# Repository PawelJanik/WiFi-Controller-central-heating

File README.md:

WiFi controller (central heating)

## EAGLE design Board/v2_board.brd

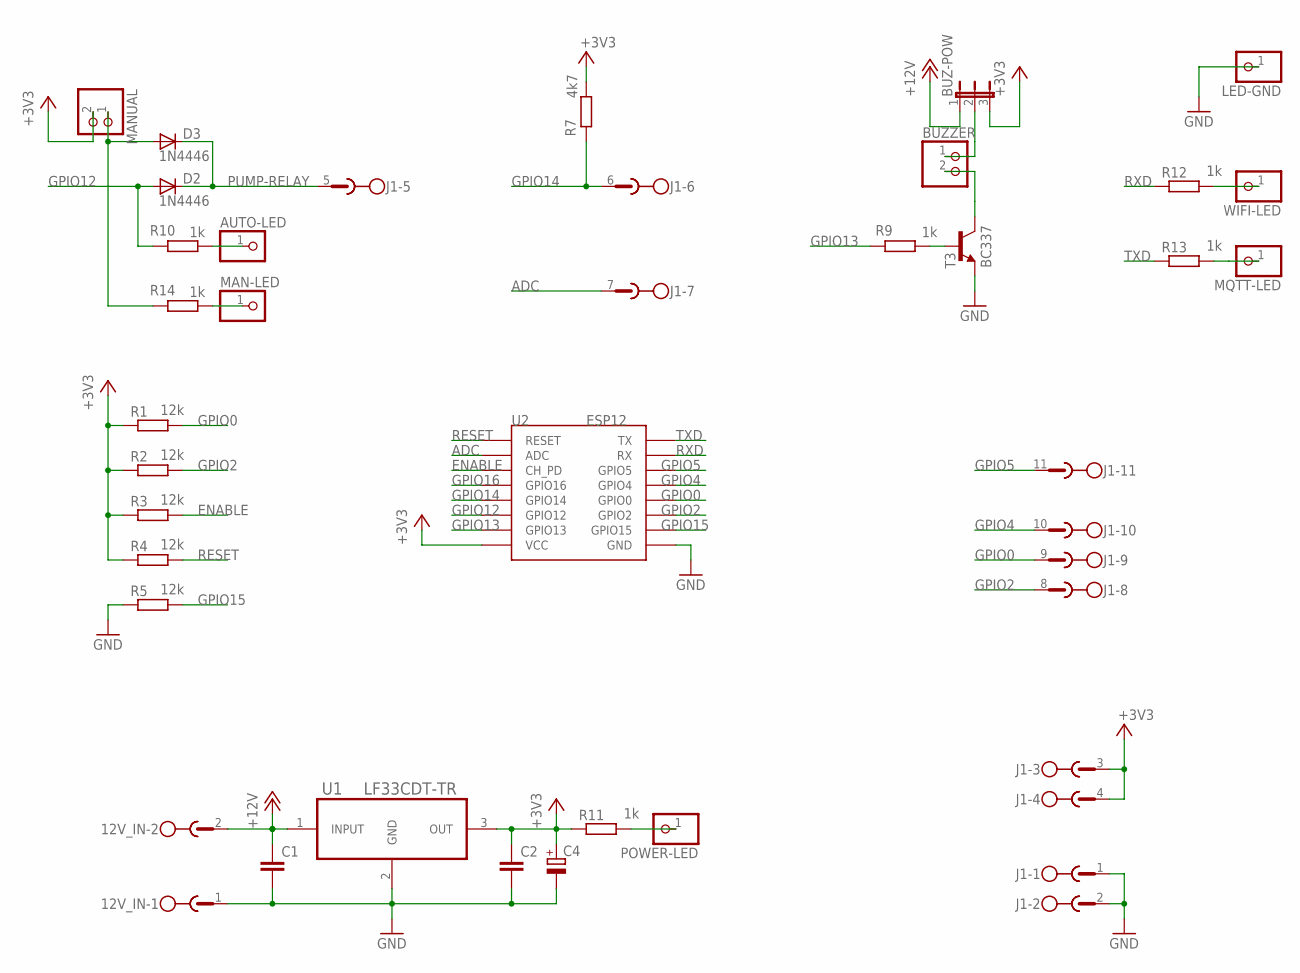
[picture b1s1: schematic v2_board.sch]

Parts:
12V_IN: MSTBA2
AUTO-LED: PINHD-1X1; 1X01
BUZ-POW: JP2E; JP2
BUZZER: PINHD-1X2; 1X02
C1, C2: C-EU025-025X050; C025-025X050
C4: CPOL-EUE3.5-8; E3,5-8
D2, D3: 1N4446; DO35-10
J1: MSTBA11
LED-GND: PINHD-1X1; 1X01
MAN-LED: PINHD-1X1; 1X01
MANUAL: PINHD-1X2; 1X02
MQTT-LED: PINHD-1X1; 1X01
POWER-LED: PINHD-1X1; 1X01
R1, R2, R3, R4, R5: 12k; R1206
R7: 4k7; R1206
R9, R10, R11, R12, R13, R14: 1k; R1206
T3: BC337; TO92
U1: LF33CDT-TR; TO228P972X240-3N
U2: ESP12
WIFI-LED: PINHD-1X1; 1X01

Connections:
+3V3: BUZ-POW.3, C2.1, C4.+, J1.3, J1.4, MANUAL.2, R1.1, R2.1, R3.1, R4.1, R7.1, R11.1, U1.3 (OUT), U2.VCC
+12V: 12V_IN.2, BUZ-POW.1, C1.1, U1.1 (INPUT)
ADC: J1.7, U2.ADC
ENABLE: R3.2, U2.CH_PD
GND: 12V_IN.1, C1.2, C2.2, C4.-, J1.1, J1.2, LED-GND.1, R5.1, T3.1 (E), U1.2 (GND), U2.GND
GPIO0: J1.9, R1.2, U2.GPIO0
GPIO2: J1.8, R2.2, U2.GPIO2
GPIO4: J1.10, U2.GPIO5 (GPIO4)
GPIO5: J1.11, U2.GPIO4 (GPIO5)
GPIO12: D2.A, R10.2, U2.GPIO12
GPIO13: R9.2, U2.GPIO13
GPIO14: J1.6, R7.2, U2.GPIO14
GPIO15: R5.2, U2.GPIO15
GPIO16: U2.GPIO16
unnamed: D3.A, MANUAL.1, R14.2
unnamed: BUZZER.2, T3.3 (C)
unnamed: R9.1, T3.2 (B)
unnamed: BUZ-POW.2, BUZZER.1
unnamed: POWER-LED.1, R11.2
unnamed: R12.2, WIFI-LED.1
unnamed: MQTT-LED.1, R13.2
unnamed: AUTO-LED.1, R10.1
unnamed: MAN-LED.1, R14.1
PUMP-RELAY: D2.C, D3.C, J1.5
RESET: R4.2, U2.RESET
RXD: R12.1, U2.RX
TXD: R13.1, U2.TX

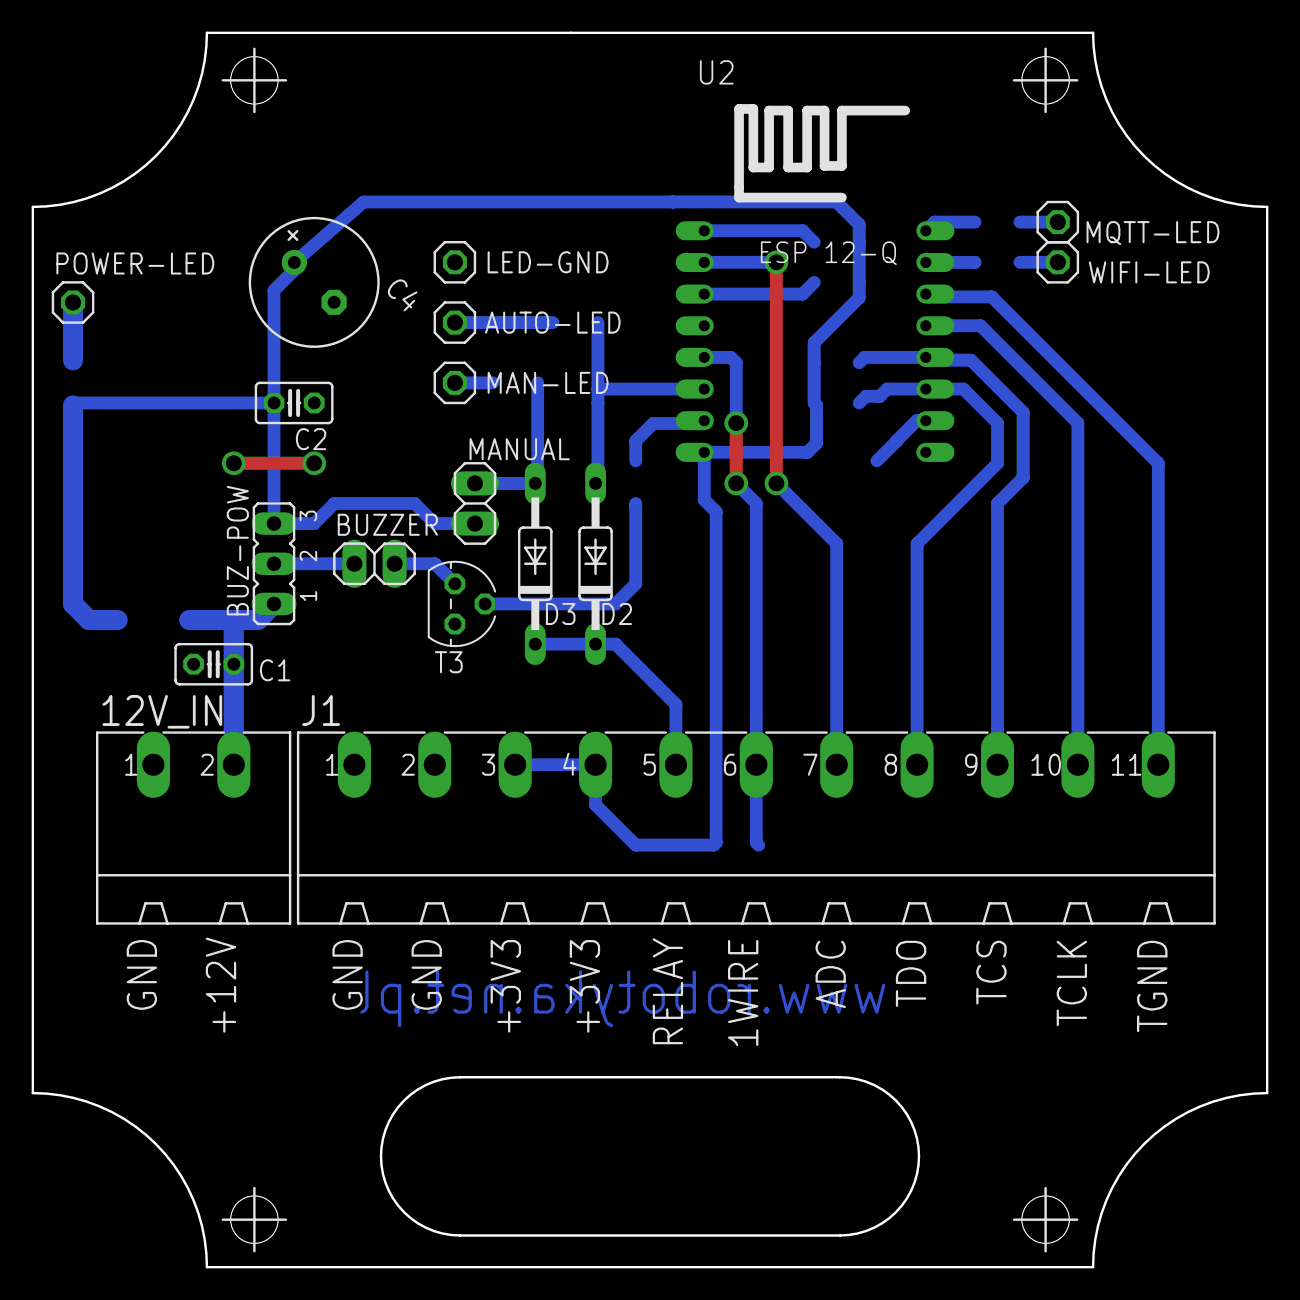
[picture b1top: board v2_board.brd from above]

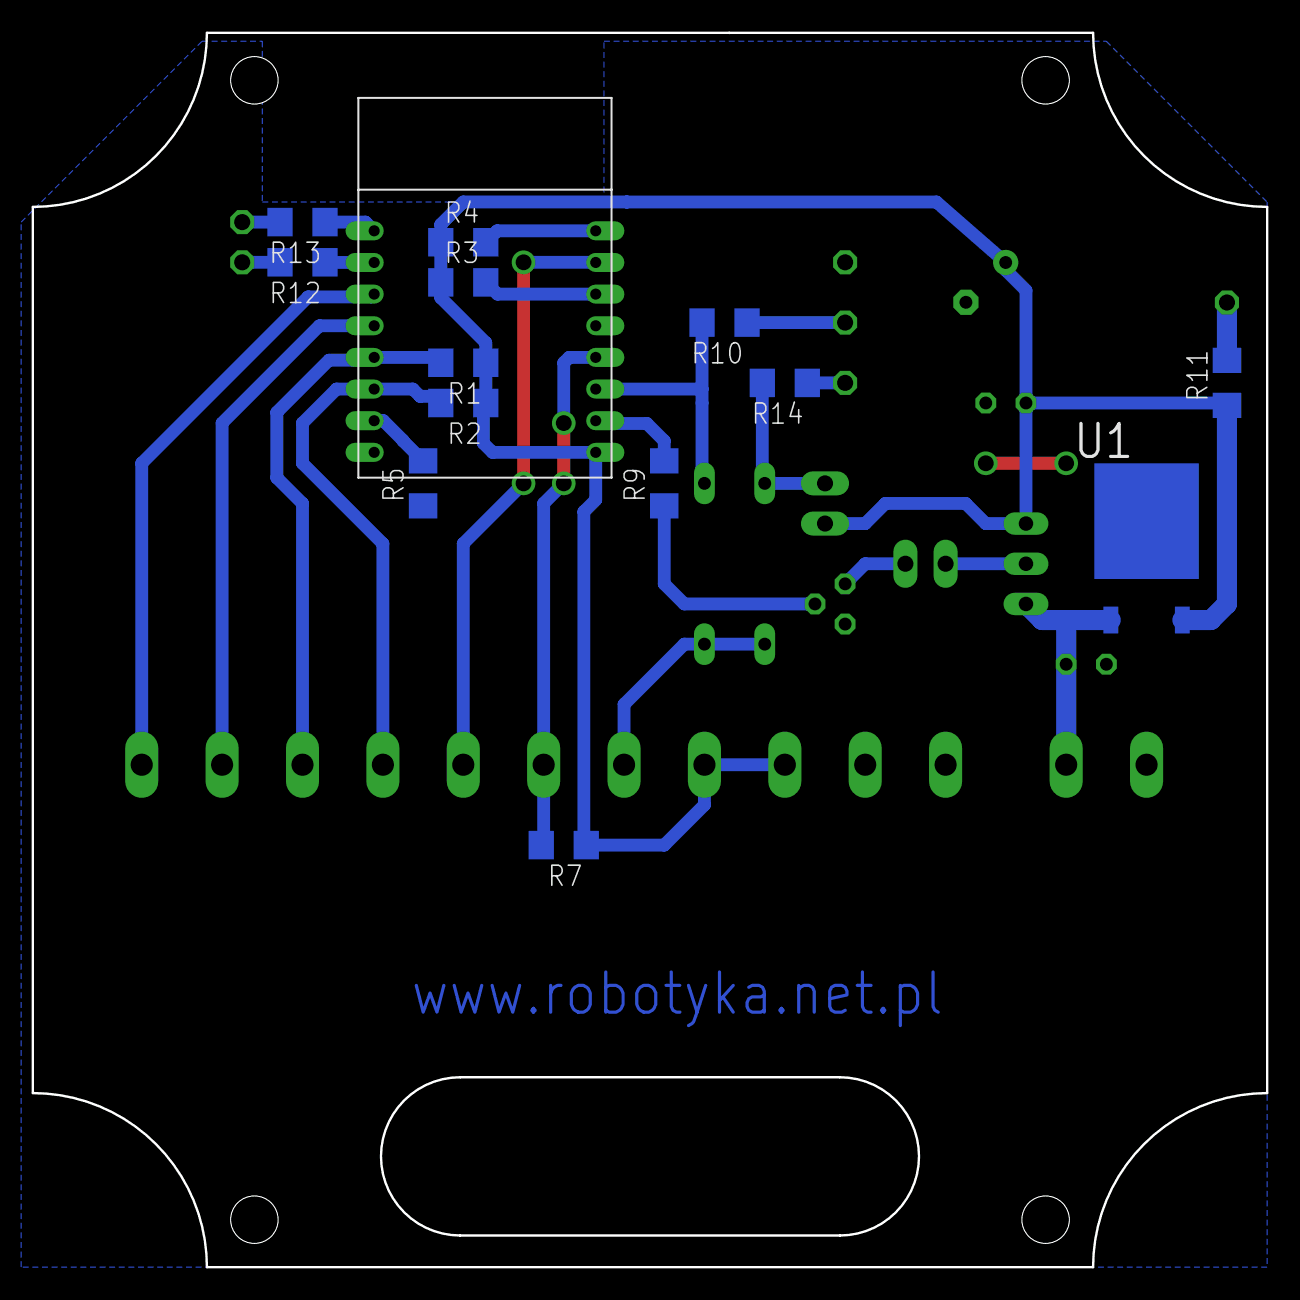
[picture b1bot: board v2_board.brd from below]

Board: 2 copper layers, 78.0 x 78.0 mm, 31 parts (13 on the bottom side), 26 nets.

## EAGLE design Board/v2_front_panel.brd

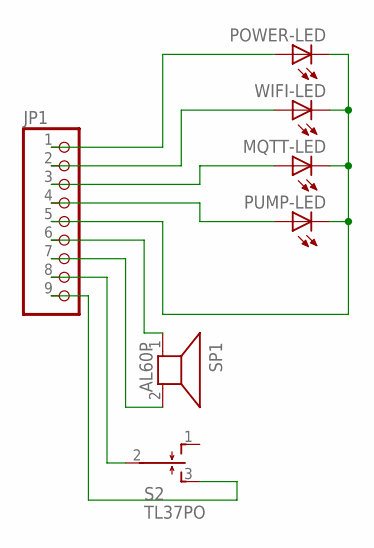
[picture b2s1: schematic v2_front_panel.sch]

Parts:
JP1: PINHD-1X9; 1X09
MQTT-LED: LED3MM
POWER-LED: LED3MM
PUMP-LED: LED3MM
S2: TL37PO; TL3XPO
SP1: AL60P
WIFI-LED: LED3MM

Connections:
GND: JP1.5, MQTT-LED.K (C), POWER-LED.K (C), PUMP-LED.K (C), WIFI-LED.K (C)
unnamed: JP1.6, SP1.1
unnamed: JP1.7, SP1.2
unnamed: JP1.1, POWER-LED.A
unnamed: JP1.2, WIFI-LED.A
unnamed: JP1.3, MQTT-LED.A
unnamed: JP1.4, PUMP-LED.A
unnamed: JP1.8, S2.2
unnamed: JP1.9, S2.3 (S)

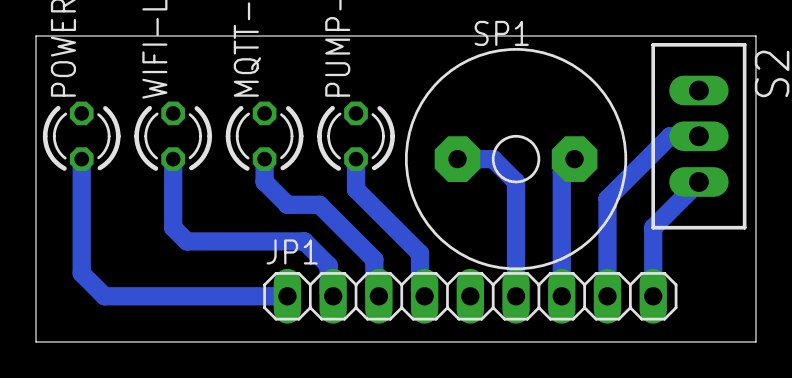
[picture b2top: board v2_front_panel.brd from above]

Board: 2 copper layers, 40.0 x 17.0 mm, 7 parts (0 on the bottom side), 9 nets.

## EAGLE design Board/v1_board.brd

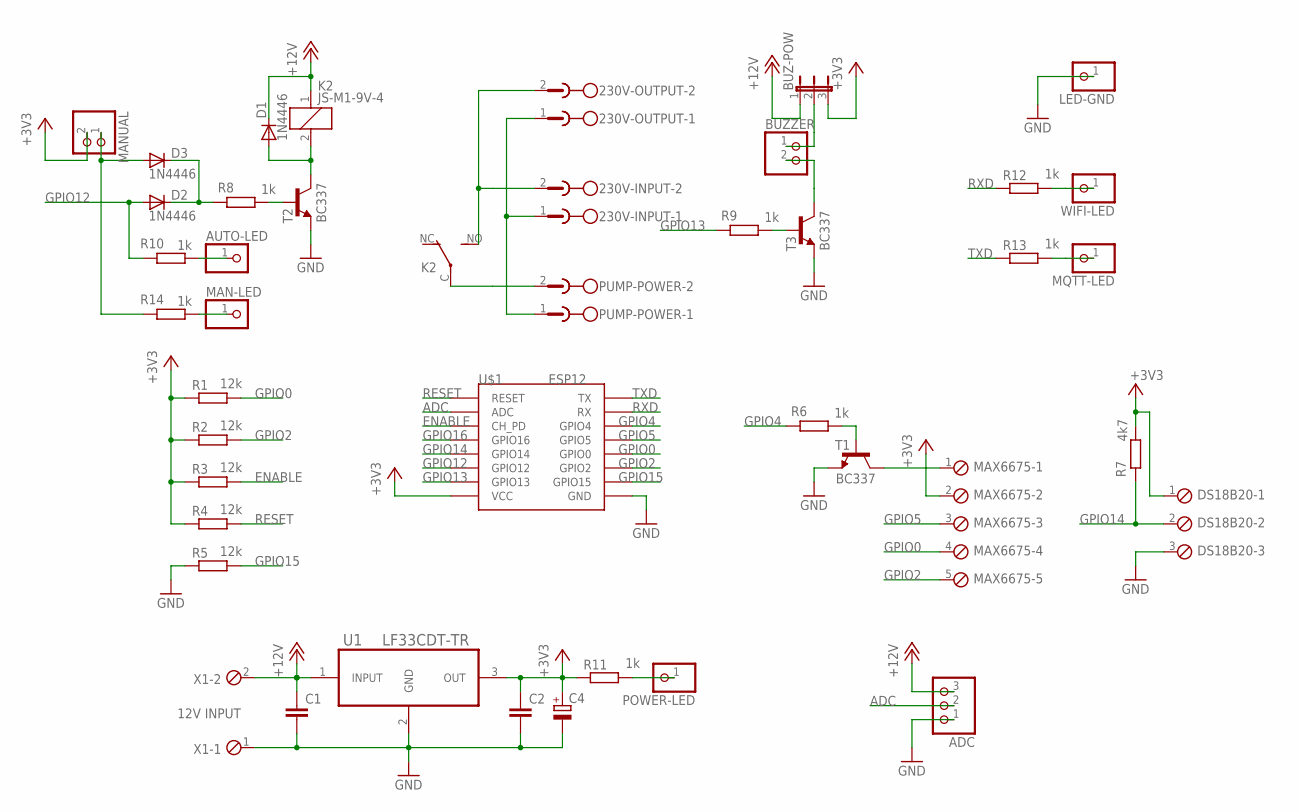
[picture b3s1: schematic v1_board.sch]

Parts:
230V-INPUT, 230V-OUTPUT: MSTBV2
ADC: PINHD-1X3; 1X03
AUTO-LED: PINHD-1X1; 1X01
BUZ-POW: JP2E; JP2
BUZZER: PINHD-1X2; 1X02
C1, C2: C-EU025-025X050; C025-025X050
C4: CPOL-EUE3.5-8; E3,5-8
D1, D2, D3: 1N4446; DO35-10
DS18B20: MPT3; 3POL254
K2: JS-M1-9V-4; JS-M
LED-GND: PINHD-1X1; 1X01
MAN-LED: PINHD-1X1; 1X01
MANUAL: PINHD-1X2; 1X02
MAX6675: MPT5; 5POL254
MQTT-LED: PINHD-1X1; 1X01
POWER-LED: PINHD-1X1; 1X01
PUMP-POWER: MSTBV2
R1, R2, R3, R4, R5: 12k; R1206
R6, R8, R9, R10, R11, R12, R13, R14: 1k; R1206
R7: 4k7; R1206
T1, T2, T3: BC337; TO92
U1: LF33CDT-TR; TO228P972X240-3N
U$1: ESP12
WIFI-LED: PINHD-1X1; 1X01
X1: 12V INPUT; 2POL254

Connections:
+3V3: BUZ-POW.3, C2.1, C4.+, DS18B20.1, MANUAL.2, MAX6675.2, R1.1, R2.1, R3.1, R4.1, R7.1, R11.1, U1.3 (OUT), U$1.VCC
+12V: ADC.3, BUZ-POW.1, C1.1, D1.C, K2.1, U1.1 (INPUT), X1.2
ADC: ADC.2, U$1.ADC
ENABLE: R3.2, U$1.CH_PD
GND: ADC.1, C1.2, C2.2, C4.-, DS18B20.3, LED-GND.1, R5.1, T1.1 (E), T2.1 (E), T3.1 (E), U1.2 (GND), U$1.GND, X1.1
GPIO0: MAX6675.4, R1.2, U$1.GPIO0
GPIO2: MAX6675.5, R2.2, U$1.GPIO2
GPIO4: R6.2, U$1.GPIO4
GPIO5: MAX6675.3, U$1.GPIO5
GPIO12: D2.A, R10.2, U$1.GPIO12
GPIO13: R9.2, U$1.GPIO13
GPIO14: DS18B20.2, R7.2, U$1.GPIO14
GPIO15: R5.2, U$1.GPIO15
GPIO16: U$1.GPIO16
unnamed: MAX6675.1, T1.3 (C)
unnamed: R6.1, T1.2 (B)
unnamed: 230V-INPUT.1, 230V-OUTPUT.1, PUMP-POWER.1
unnamed: D1.A, K2.2, T2.3 (C)
unnamed: D3.A, MANUAL.1, R14.2
unnamed: R8.1, T2.2 (B)
unnamed: BUZZER.2, T3.3 (C)
unnamed: R9.1, T3.2 (B)
unnamed: BUZ-POW.2, BUZZER.1
unnamed: K2.C, PUMP-POWER.2
unnamed: POWER-LED.1, R11.2
unnamed: R12.2, WIFI-LED.1
unnamed: MQTT-LED.1, R13.2
unnamed: 230V-INPUT.2, 230V-OUTPUT.2, K2.NO (S)
unnamed: AUTO-LED.1, R10.1
unnamed: MAN-LED.1, R14.1
unnamed: D2.C, D3.C, R8.2
RESET: R4.2, U$1.RESET
RXD: R12.1, U$1.RX
TXD: R13.1, U$1.TX

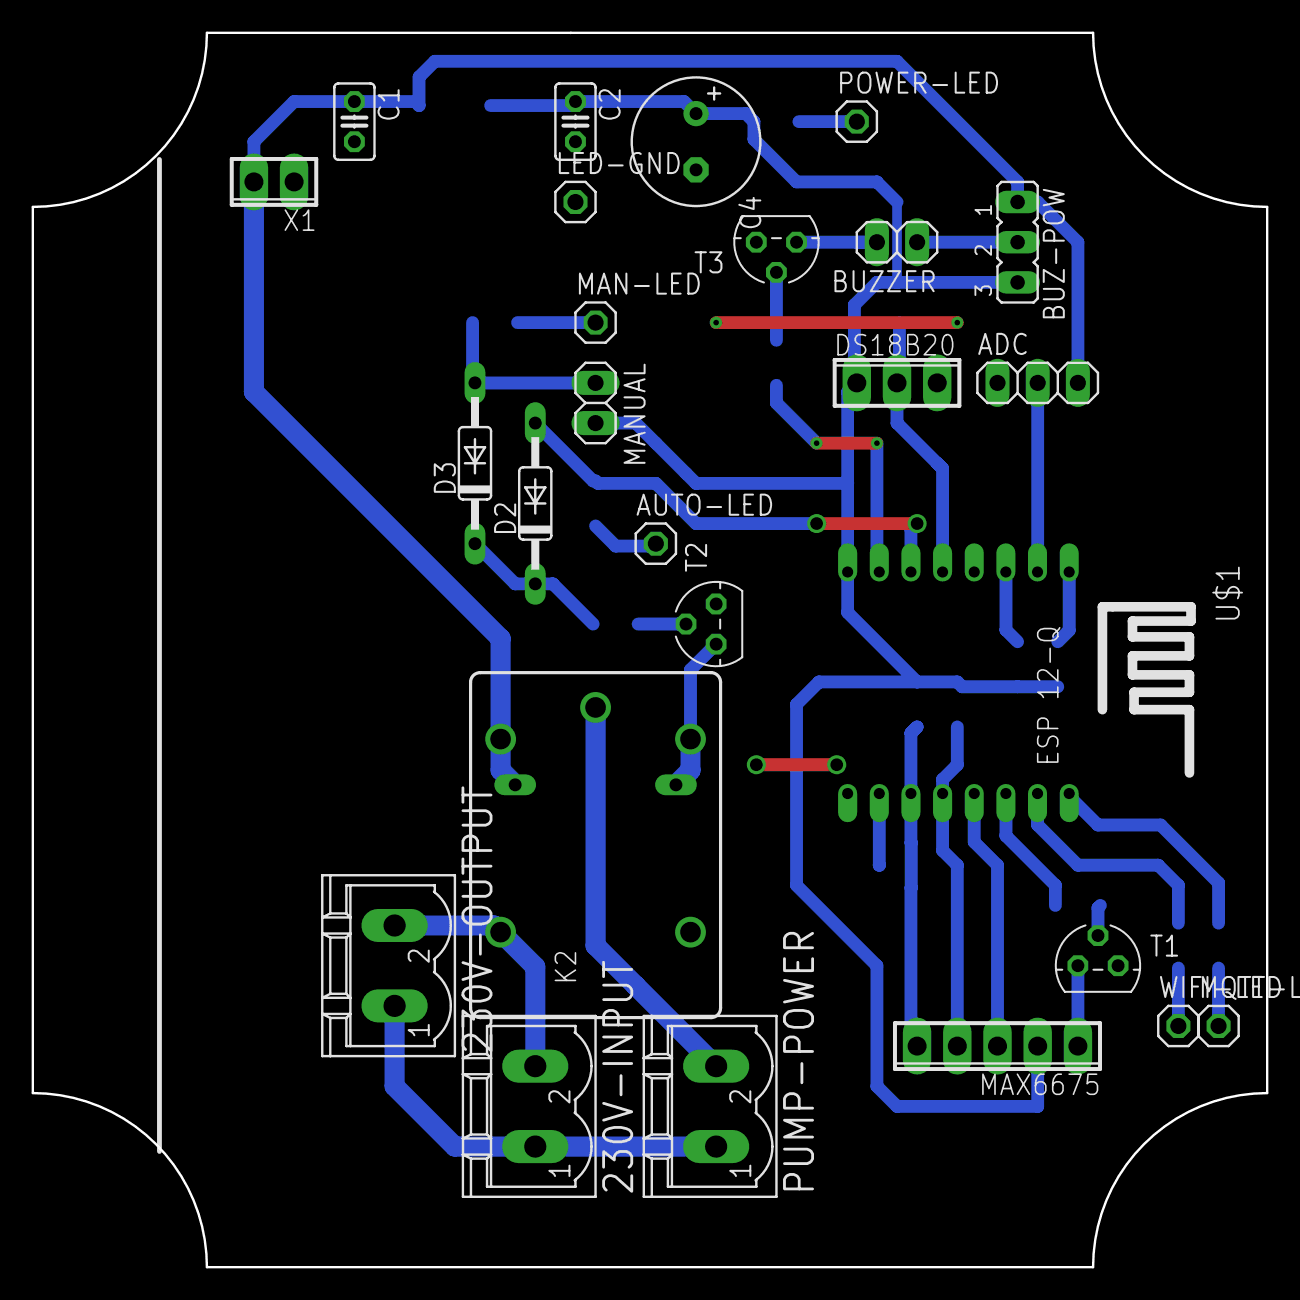
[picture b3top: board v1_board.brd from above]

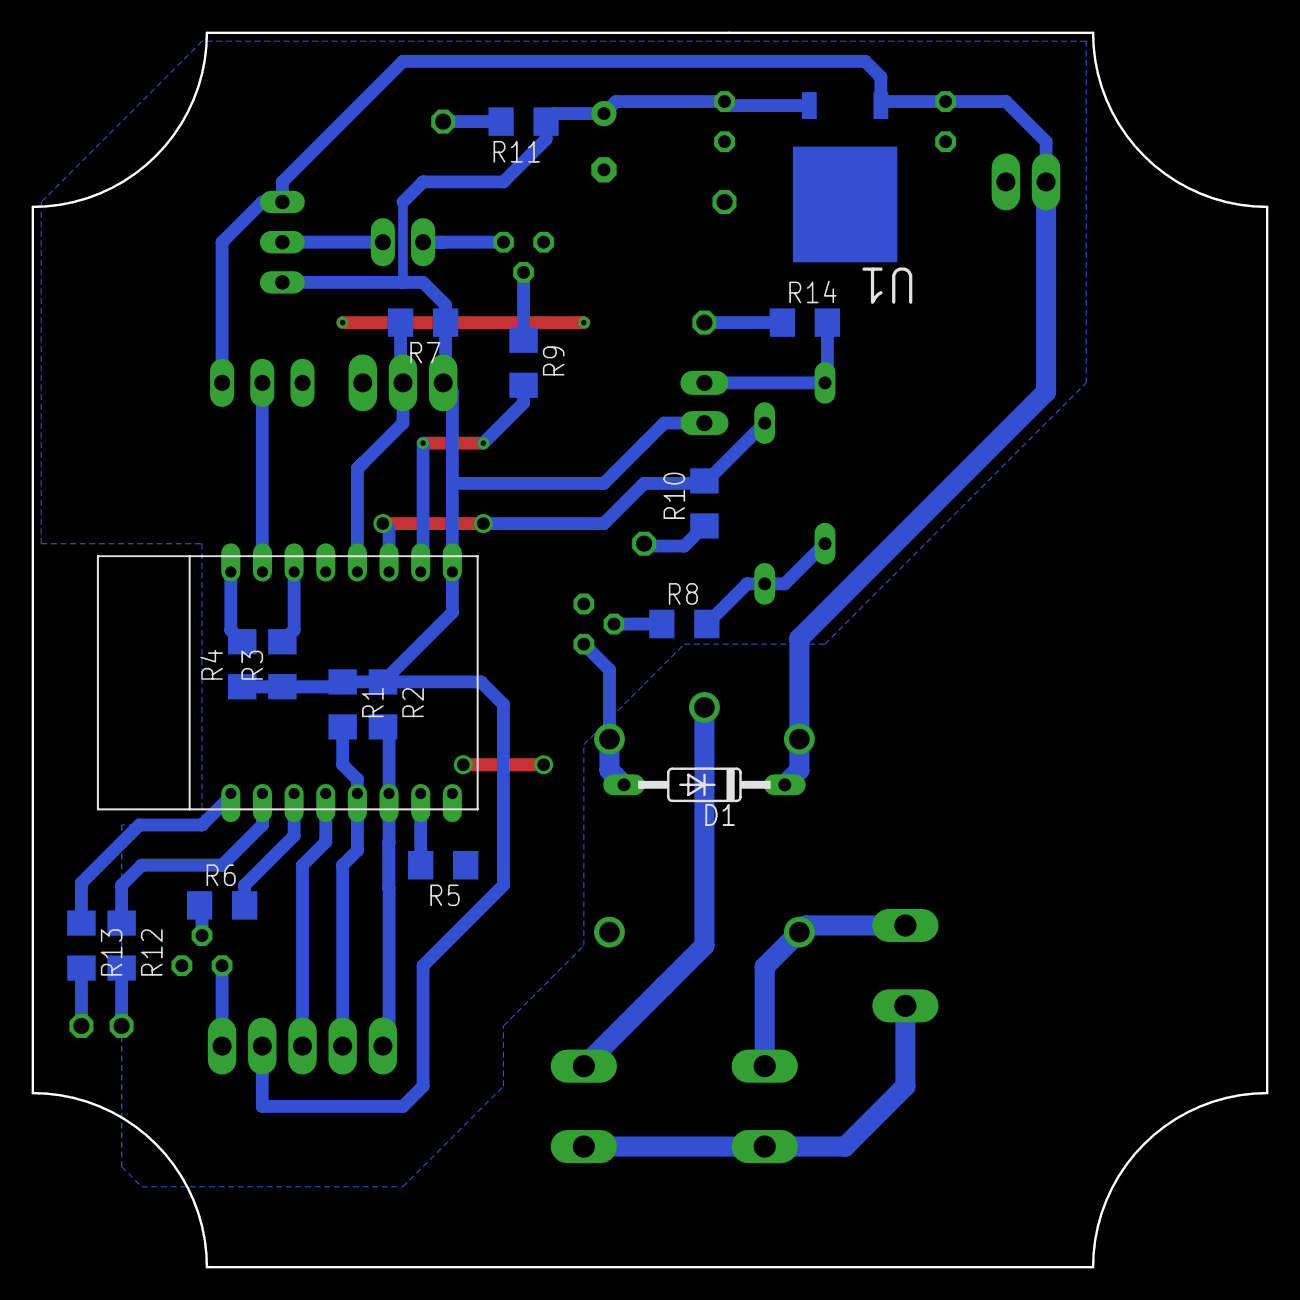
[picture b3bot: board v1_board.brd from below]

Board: 2 copper layers, 78.0 x 78.0 mm, 42 parts (16 on the bottom side), 33 nets.

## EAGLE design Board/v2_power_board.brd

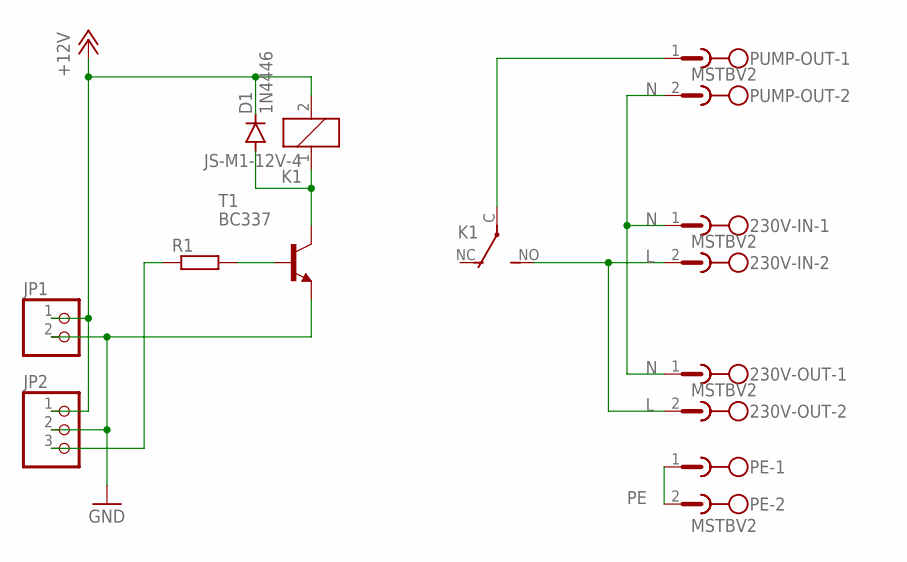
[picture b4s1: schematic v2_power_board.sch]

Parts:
230V-IN, 230V-OUT: MSTBV2
D1: 1N4446; DO35-10
JP1: PINHD-1X2; 1X02
JP2: PINHD-1X3; 1X03
K1: JS-M1-12V-4; JS-M
PE: MSTBV2
PUMP-OUT: MSTBV2
R1: R-EU_R1206; R1206
T1: BC337; TO92

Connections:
+12V: D1.C, JP1.1, JP2.1, K1.2
GND: JP1.2, JP2.2, T1.1 (E)
L: 230V-IN.2, 230V-OUT.2, K1.NO (S)
N: 230V-IN.1, 230V-OUT.1, PUMP-OUT.2
unnamed: K1.C, PUMP-OUT.1
unnamed: R1.2, T1.2 (B)
unnamed: D1.A, K1.1, T1.3 (C)
unnamed: JP2.3, R1.1
PE: PE.1, PE.2

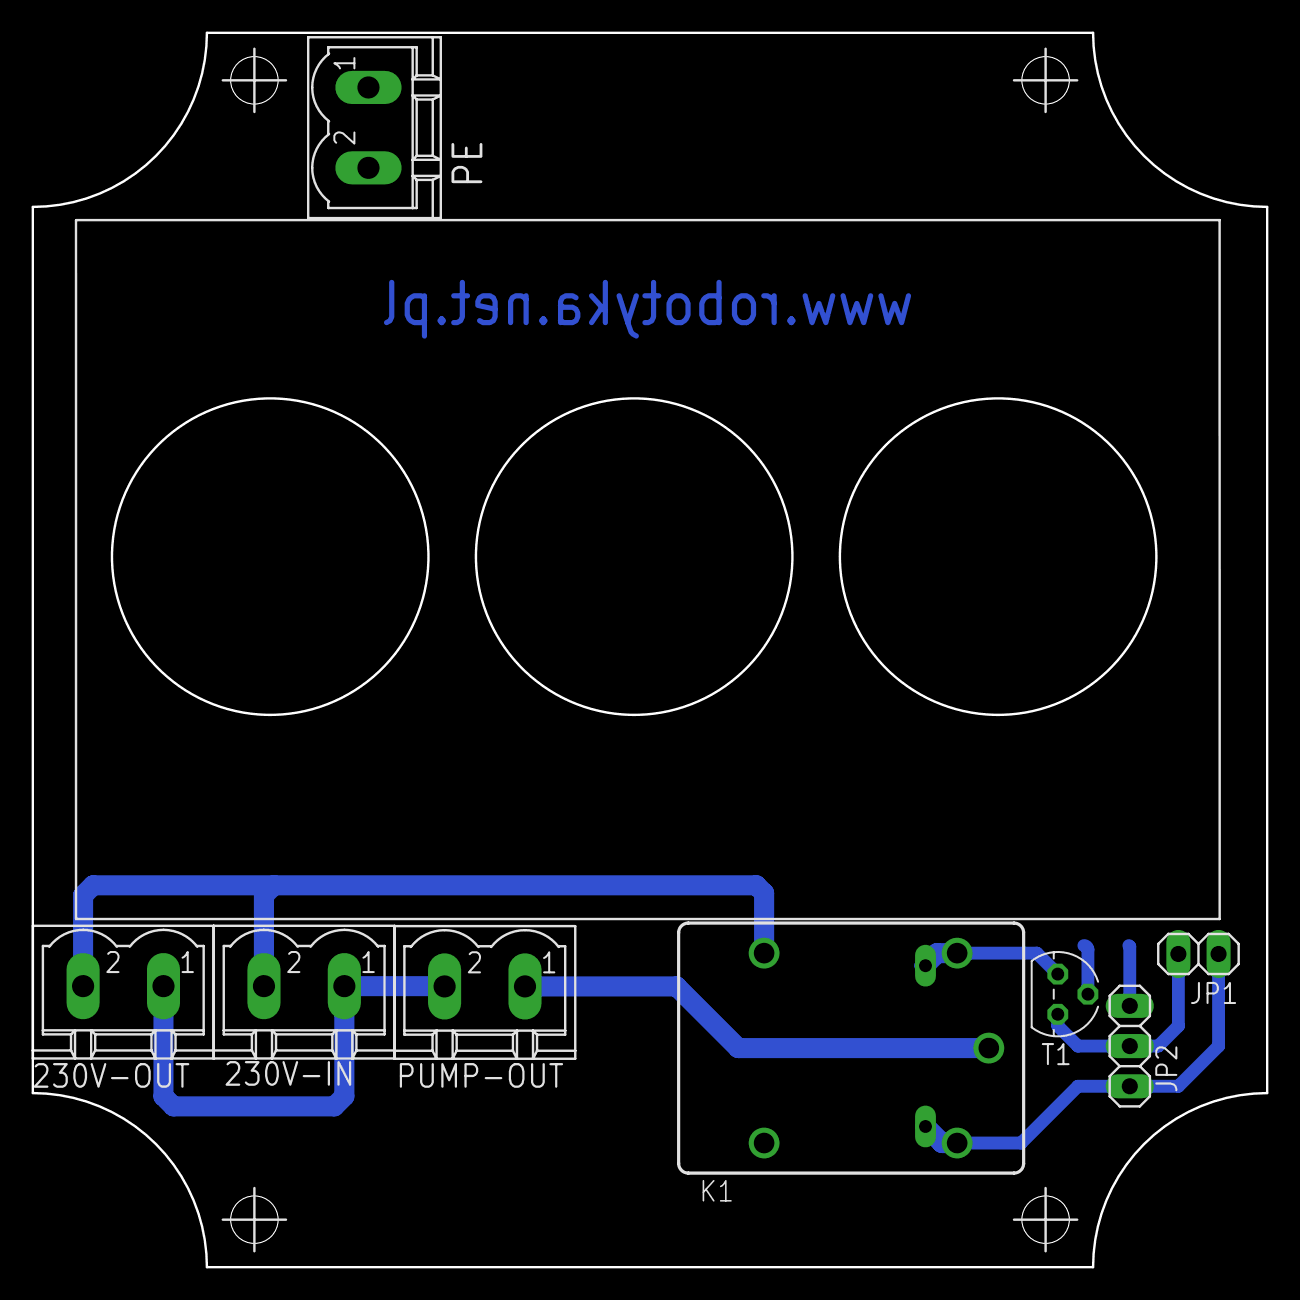
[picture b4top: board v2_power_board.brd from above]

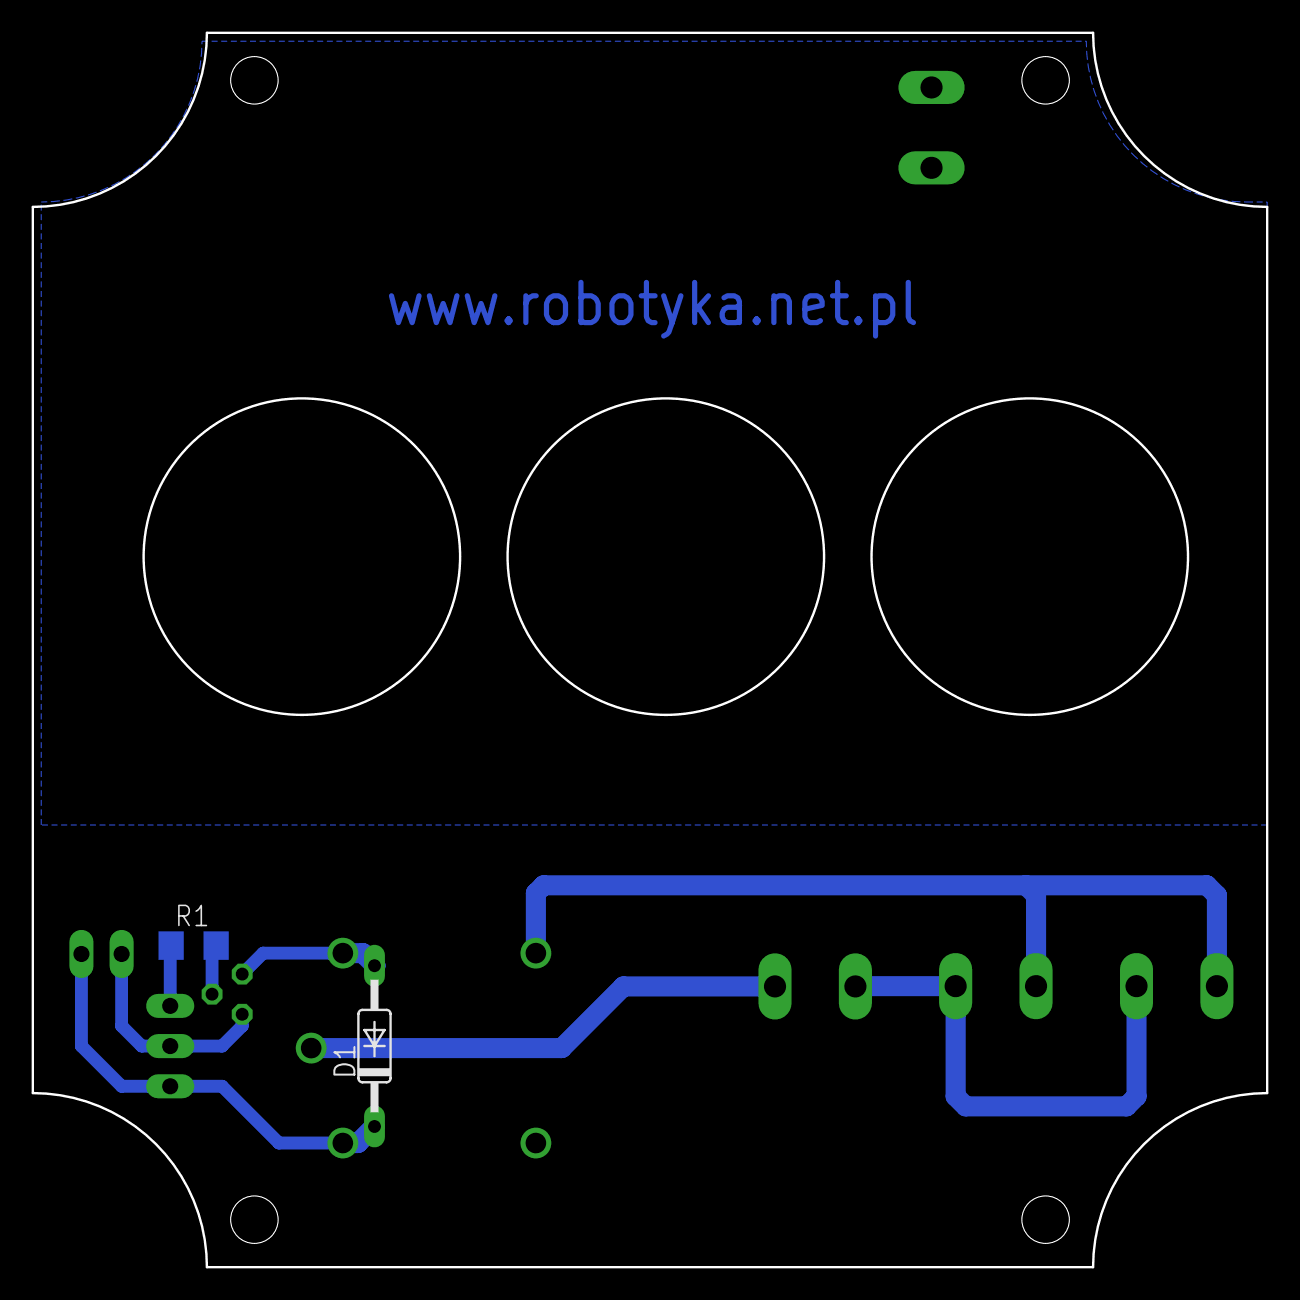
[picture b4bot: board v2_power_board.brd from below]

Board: 2 copper layers, 78.0 x 78.0 mm, 10 parts (2 on the bottom side), 9 nets.

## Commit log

2018-12-17 Change folder name
2018-12-21 Front panel board update
2018-12-22 fixed library esp12
2018-12-24 Fixed alarm and add restart function
2019-01-05 Project migration to PlatformIO
